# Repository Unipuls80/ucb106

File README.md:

# ucb106
MH106 control board for Unidisp universal display 
- rev. 1.2 05/2024: added V6, R16

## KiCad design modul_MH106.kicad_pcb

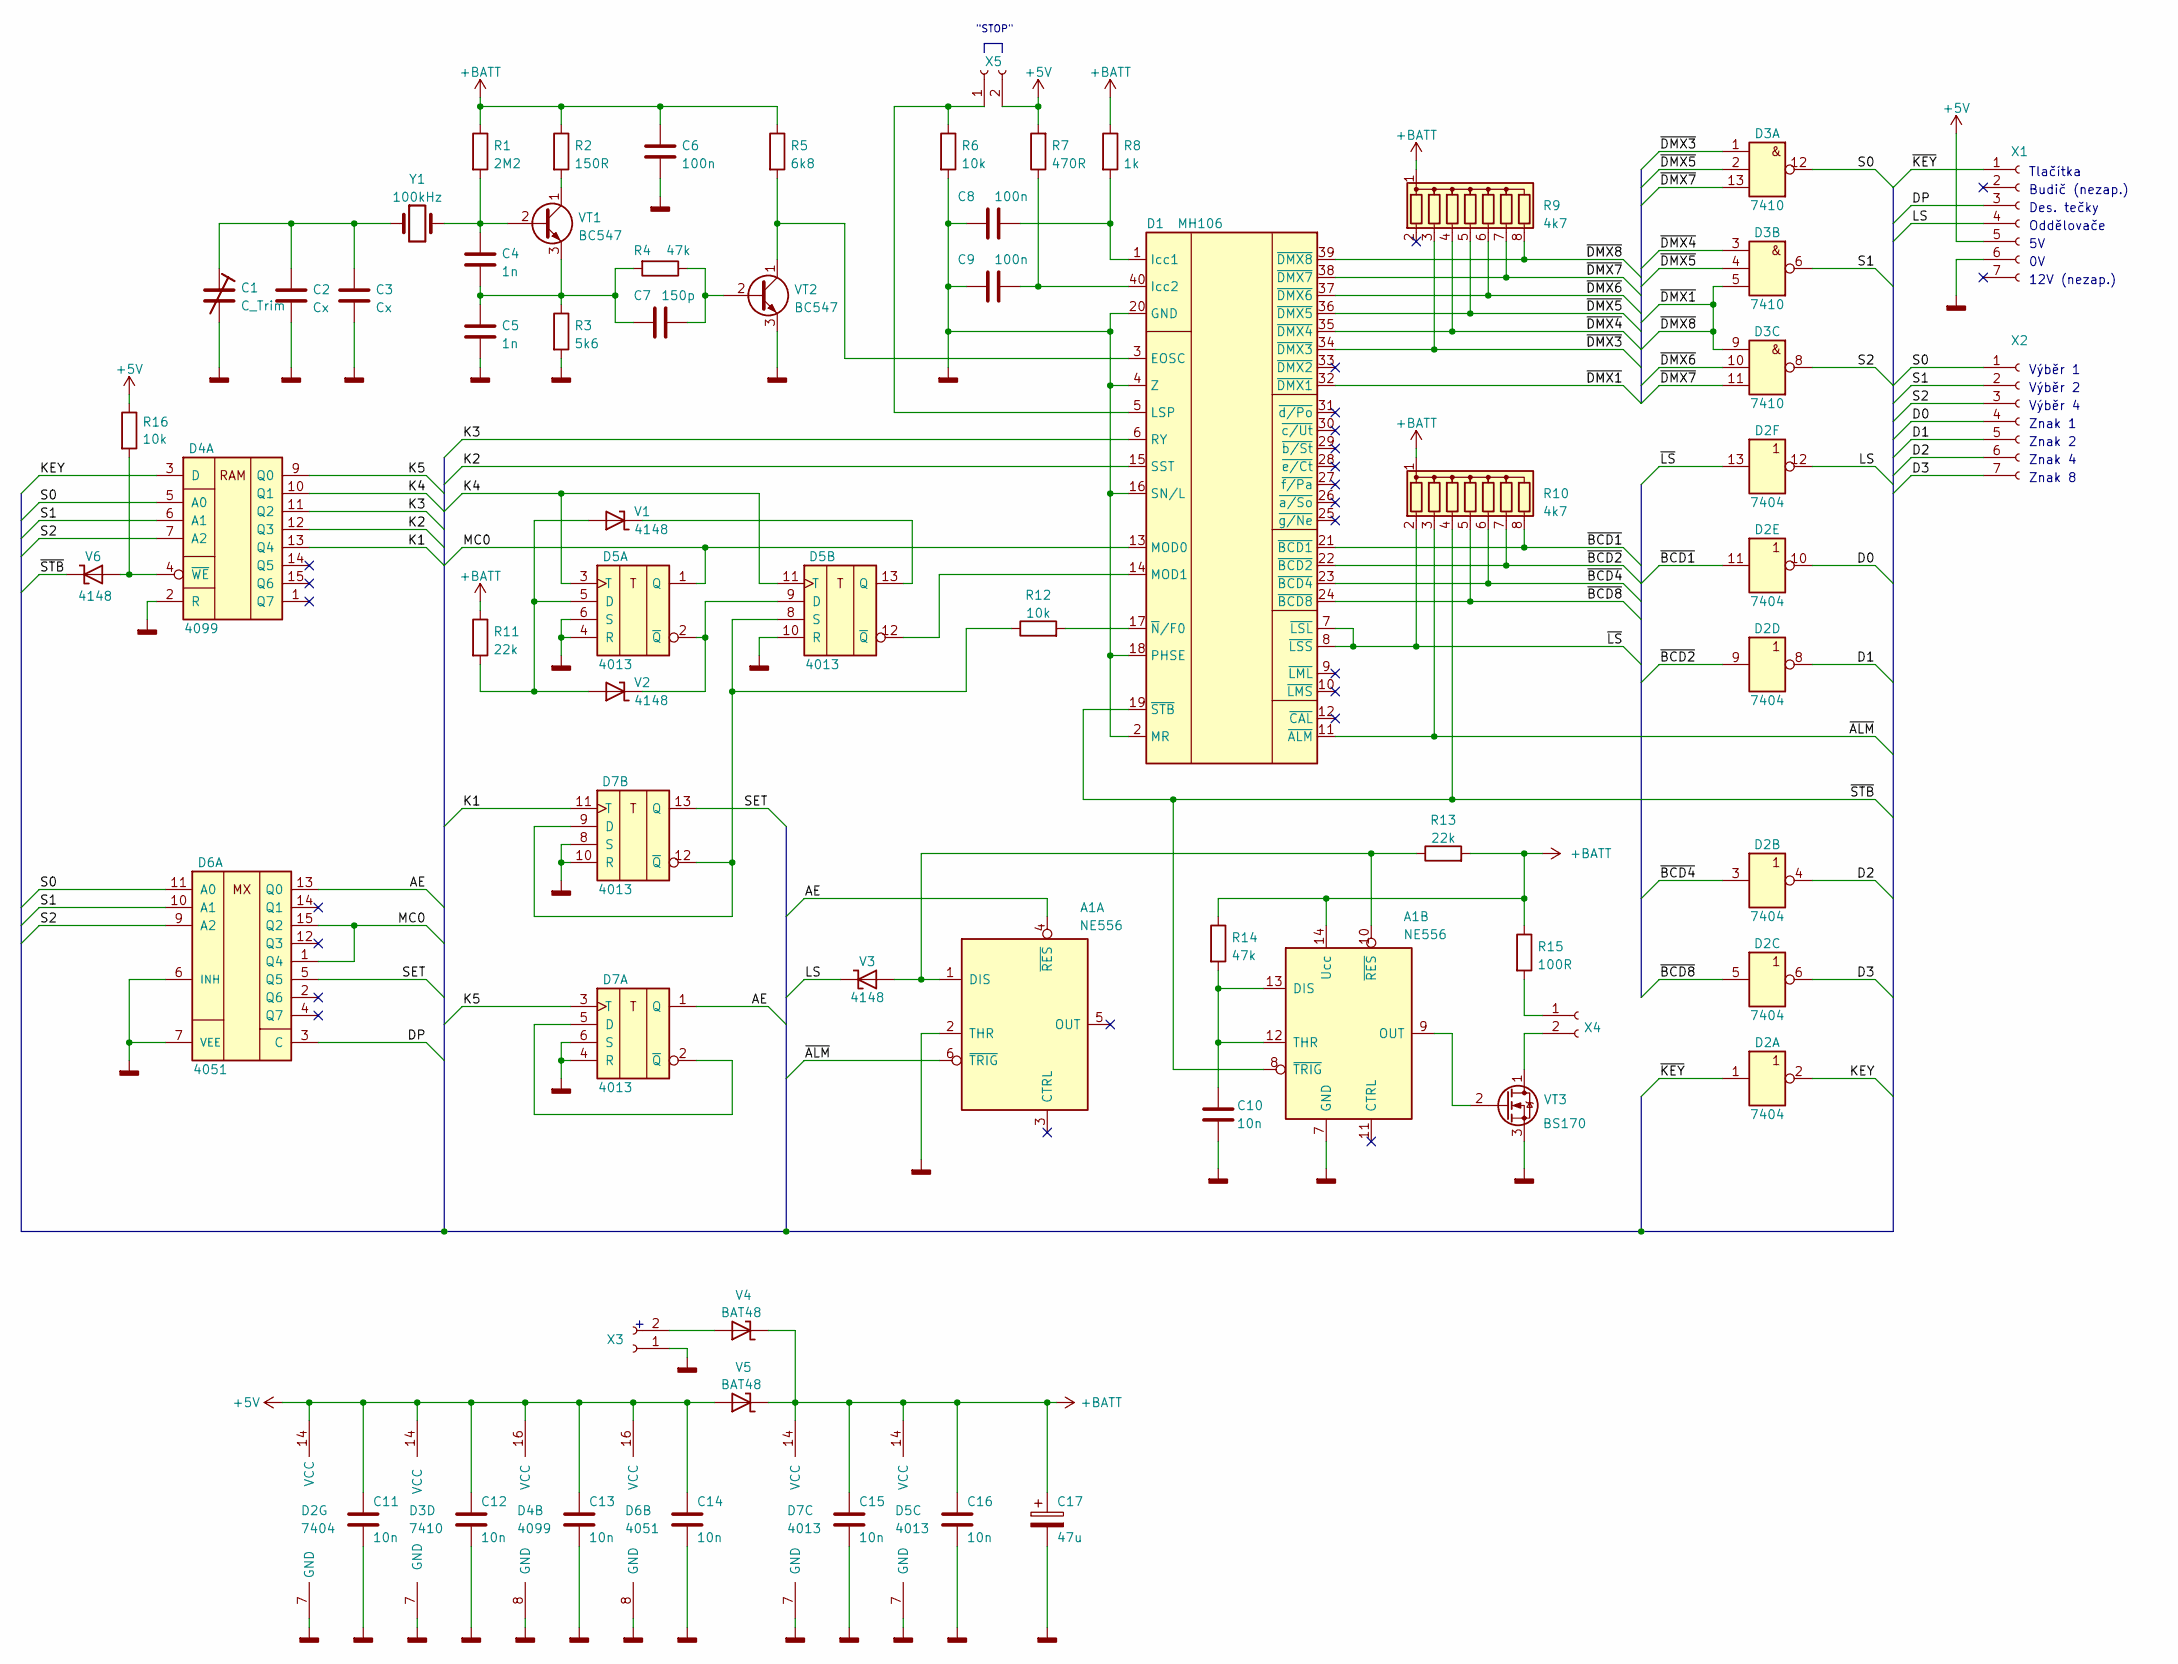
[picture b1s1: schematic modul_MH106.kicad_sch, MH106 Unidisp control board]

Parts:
A1: NE556; DIP-14_W7.62mm
C1: C_Trim; C_trim_THT
C2, C3: Cx; C_Disc_D4.3mm_W1.9mm_P5.00mm
C4, C5: 1n; C_Disc_D4.3mm_W1.9mm_P5.00mm
C6, C8, C9: 100n; C_Disc_D4.3mm_W1.9mm_P5.00mm
C7: 150p; C_Disc_D4.3mm_W1.9mm_P5.00mm
C10, C11, C12, C13, C14, C15, C16: 10n; C_Disc_D4.3mm_W1.9mm_P5.00mm
C17: 47u; C_Radial_D5.0mm_H5.0mm_P2.00mm
D1: MH106; DIP-40_W15.24mm
D2: 7404; DIP-14_W7.62mm
D3: 7410; DIP-14_W7.62mm
D4: 4099; DIP-16_W7.62mm
D5, D7: 4013; DIP-14_W7.62mm
D6: 4051; DIP-16_W7.62mm
R1: 2M2; R DIN0207 10.16mm
R2: 150R; R DIN0207 10.16mm
R3: 5k6; R DIN0207 10.16mm
R4, R14: 47k; R DIN0207 10.16mm
R5: 6k8; R DIN0207 10.16mm
R6, R12, R16: 10k; R DIN0207 10.16mm
R7: 470R; R DIN0207 10.16mm
R8: 1k; R DIN0207 10.16mm
R9, R10: 4k7; R_Array_SIP8
R11, R13: 22k; R DIN0207 10.16mm
R15: 100R; R DIN0207 10.16mm
V1, V2, V3, V6: 4148; D_DO-35_SOD27_P10.16mm_Horizontal
V4, V5: BAT48; D_DO-35_SOD27_P10.16mm_Horizontal
VT1, VT2: BC547; TO-92L_Wide
VT3: BS170; TO-92L_Wide
X1, X2: Conn_01x07_Female; PinSocket_1x07_P2.54mm_Vertical
X3: BATT; PinSocket_1x02_P2.54mm_Vertical
X4: SPKR; PinSocket_1x02_P2.54mm_Vertical
X5: Conn_01x02_Female; PinSocket_1x02_P2.54mm_Vertical
Y1: 100kHz; PKJ_100kHz

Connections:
+5V: C11.1, C12.1, C13.1, C14.1, D2.14 (VCC), D3.14 (VCC), D4.16 (VCC), D6.16 (VCC), R7.2, R16.1, V5.2 (A), X1.5, X5.2
+BATT: A1.14 (Ucc), C6.1, C15.1, C16.1, C17.1, D5.14 (VCC), D7.14 (VCC), R1.1, R2.1, R5.1, R8.1, R9.1 (common), R10.1 (common), R11.1, R13.2, R14.1, R15.1, V4.1 (K), V5.1 (K)
/AE: A1.4 (~RES), D6.13 (Q0), D7.1 (Q)
/D0: D2.10, X2.4
/D1: D2.8, X2.5
/D2: D2.4, X2.6
/D3: D2.6, X2.7
/DP: D6.3 (C), X1.3
/K1: D4.13 (Q4), D7.11 (T)
/K2: D1.15 (SST), D4.12 (Q3)
/K3: D1.6 (RY), D4.11 (Q2)
/K4: D4.10 (Q1), D5.3 (T), D5.11 (T)
/K5: D4.9 (Q0), D7.3 (T)
/KEY: D2.2, D4.3 (D)
/LS: D2.12, V3.1 (K), X1.4
/MC0: D1.13 (MOD0), D5.1 (Q), D6.1 (Q4), D6.15 (Q2)
/S0: D3.12, D4.5 (A0), D6.11 (A0), X2.1
/S1: D3.6, D4.6 (A1), D6.10 (A1), X2.2
/S2: D3.8, D4.7 (A2), D6.9 (A2), X2.3
/SET: D6.5 (Q5), D7.13 (Q)
/~ALM: A1.6 (~TRIG), D1.11 (~ALM), R10.3 (R2)
/~BCD1: D1.21 (~BCD1), D2.11, R10.8 (R7)
/~BCD2: D1.22 (~BCD2), D2.9, R10.7 (R6)
/~BCD4: D1.23 (~BCD4), D2.3, R10.6 (R5)
/~BCD8: D1.24 (~BCD8), D2.5, R10.5 (R4)
/~DMX1: D1.32 (~DMX1), D1.39 (~DMX8), D3.5, D3.9, R9.8 (R7)
/~DMX3: D1.34 (~DMX3), D3.1, R9.3 (R2)
/~DMX4: D1.35 (~DMX4), D3.3, R9.4 (R3)
/~DMX5: D1.36 (~DMX5), D3.2, D3.4, R9.5 (R4)
/~DMX6: D1.37 (~DMX6), D3.10, R9.6 (R5)
/~DMX7: D1.38 (~DMX7), D3.11, D3.13, R9.7 (R6)
/~KEY: D2.1, X1.1
/~LS: D1.7 (~LSL), D1.8 (~LSS), D2.13, R10.2 (R1)
/~STB: A1.8 (~TRIG), D1.19 (~STB), R10.4 (R3), V6.1 (K)
GNDD: A1.2 (THR), A1.7 (GND), C1.2, C2.2, C3.2, C5.2, C6.2, C8.1, C9.1, C10.2, C11.2, C12.2, C13.2, C14.2, C15.2, C16.2, C17.2, D1.2 (MR), D1.4 (Z), D1.16 (SN/L), D1.18 (PHSE), D1.20 (GND), D2.7 (GND), D3.7 (GND), D4.2 (R), D4.8 (GND), D5.4 (R), D5.6 (S), D5.7 (GND), D5.10 (R), D6.6 (INH), D6.7 (VEE), D6.8 (GND), D7.4 (R), D7.6 (S), D7.7 (GND), D7.8 (S), D7.10 (R), R3.2, R6.2, VT2.3 (E), VT3.3 (S), X1.6, X3.1
unnamed: A1.1 (DIS), A1.10 (~RES), R13.1, V3.2 (A)
unnamed: A1.12 (THR), A1.13 (DIS), C10.1, R14.2
unnamed: A1.9 (OUT), VT3.2 (G)
unnamed: C1.1, C2.1, C3.1, Y1.1
unnamed: D1.3 (EOSC), R5.2, VT2.1 (C)
unnamed: C8.2, D1.1 (Icc1), R8.2
unnamed: C9.2, D1.40 (Icc2), R7.1
unnamed: D1.5 (LSP), R6.1, X5.1
unnamed: D1.14 (MOD1), D5.12 (~Q)
unnamed: D1.17 (~N/F0), R12.2
unnamed: D4.4 (~WE), R16.2, V6.2 (A)
unnamed: D5.5 (D), R11.2, V1.2 (A), V2.2 (A)
unnamed: D5.2 (~Q), D5.9 (D), V2.1 (K)
unnamed: D5.13 (Q), V1.1 (K)
unnamed: D5.8 (S), D7.9 (D), D7.12 (~Q), R12.1
unnamed: D7.2 (~Q), D7.5 (D)
unnamed: V4.2 (A), X3.2
unnamed: C4.1, R1.2, VT1.2 (B), Y1.2
unnamed: R2.2, VT1.1 (C)
unnamed: C4.2, C5.1, C7.1, R3.1, R4.2, VT1.3 (E)
unnamed: C7.2, R4.1, VT2.2 (B)
unnamed: VT3.1 (D), X4.2
unnamed: R15.2, X4.1

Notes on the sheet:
Znak 1
Budič (nezap.)
Znak 8
Výběr 4
Tlačítka
Des. tečky
Oddělovače
Výběr 2
12V (nezap.)
"STOP"
Výběr 1
Znak 2
Znak 4

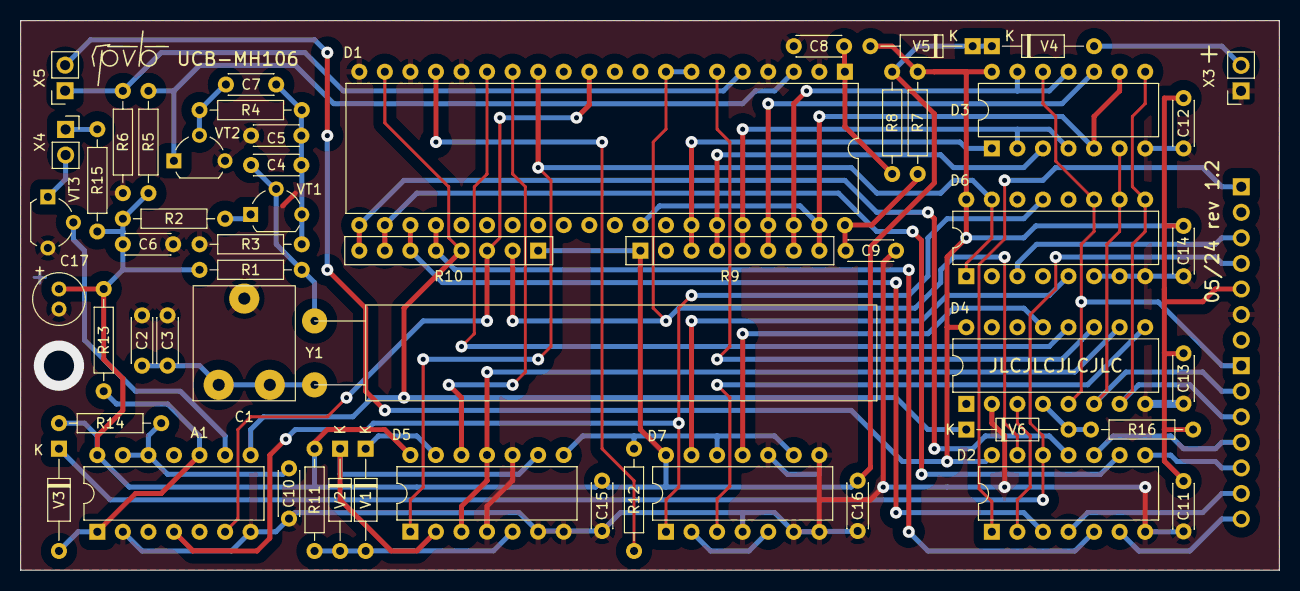
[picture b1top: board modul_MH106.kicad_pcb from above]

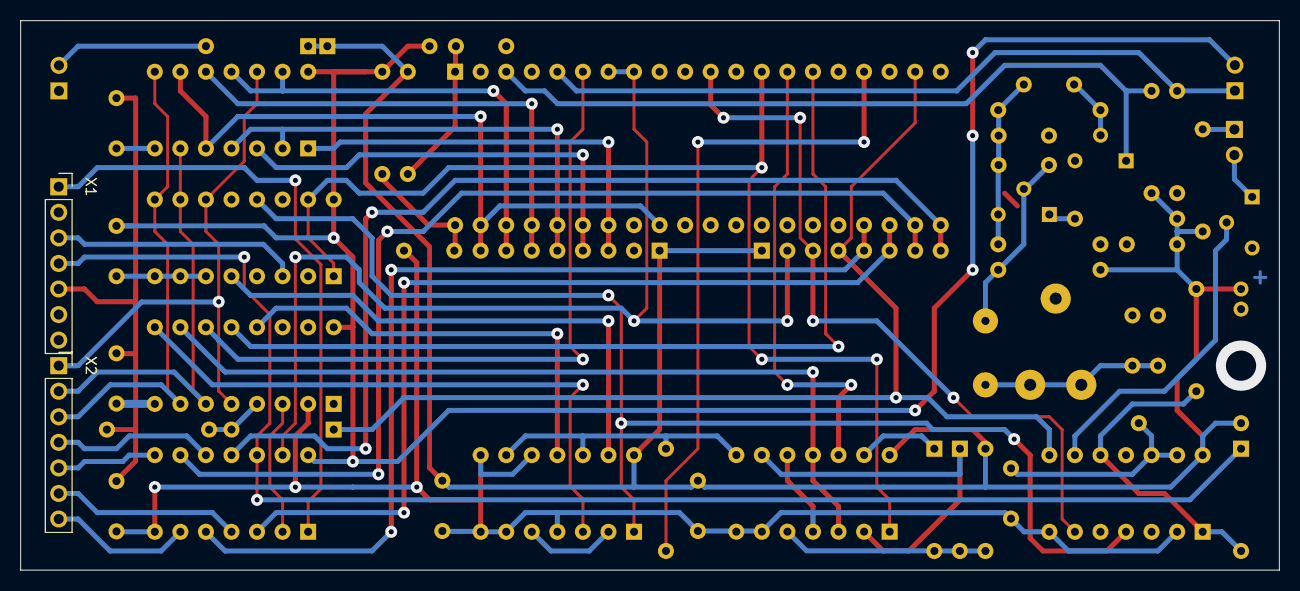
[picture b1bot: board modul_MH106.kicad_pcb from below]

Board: 2 copper layers, 125.1 x 54.6 mm, 56 parts (2 on the bottom side), 58 nets.

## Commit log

2024-05-17 Create LICENSE
